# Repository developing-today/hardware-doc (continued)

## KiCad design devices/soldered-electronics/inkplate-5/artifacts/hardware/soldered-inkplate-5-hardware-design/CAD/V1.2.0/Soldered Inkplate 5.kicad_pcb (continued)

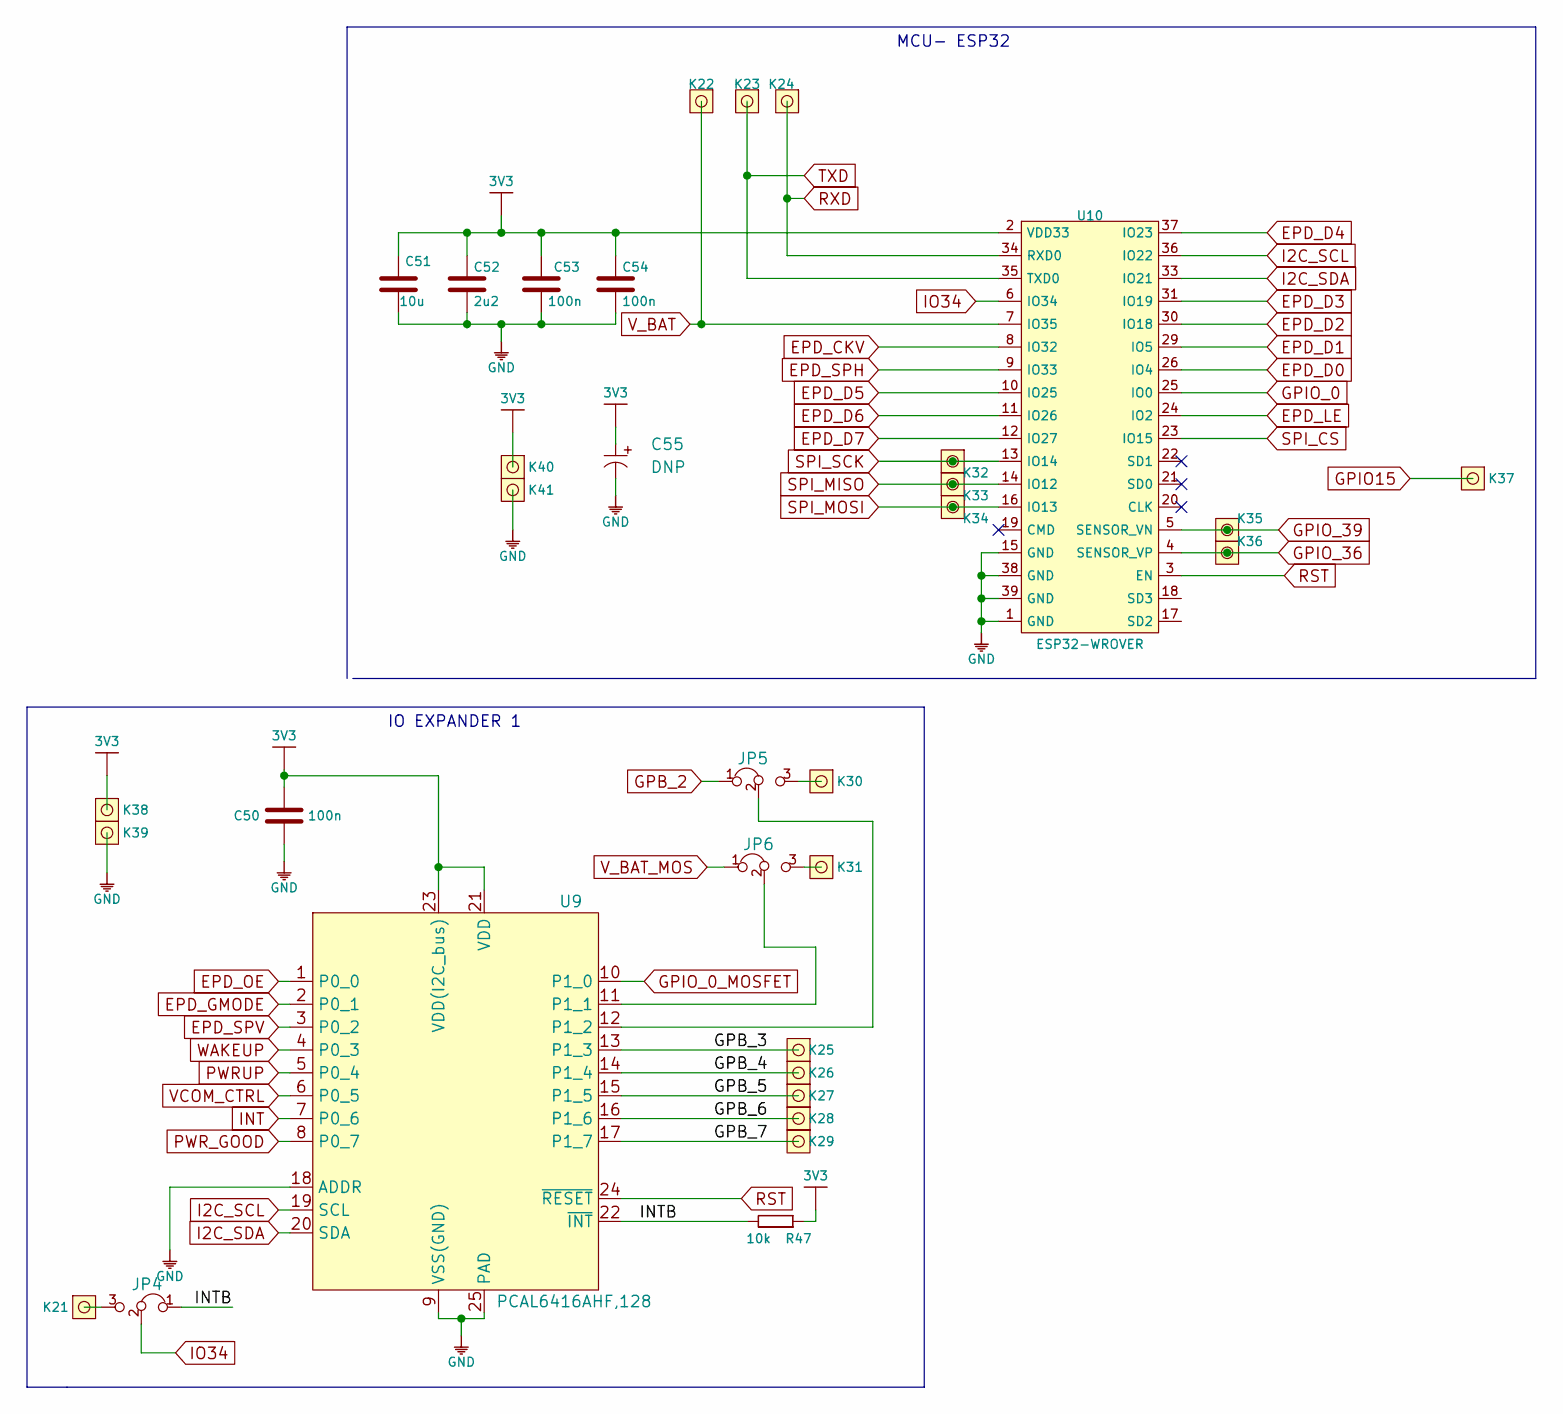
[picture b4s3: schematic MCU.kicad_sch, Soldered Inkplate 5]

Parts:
C50, C53, C54: 100n; 0603C
C51: 10u; 1206C
C52: 2u2; 0603C
C55: DNP; 2917C
JP4, JP5, JP6: SMD_JUMPER_3_PAD_CONNECTED_LEFT_TRACE
K21, K22, K23, K24, K25, K26, K27, K28, K29, K30, K31, K32, K33, K34, K35, K36, K37, K38, K39, K40, K41: HEADER_MALE_1X1_Inkplate
R47: 10k; 0603R
U9: PCAL6416AHF,128
U10: ESP32-WROVER

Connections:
3V3: C50.2, C51.2, C52.2, C53.2, C54.2, C55.1 (+), K38.1, K40.1, R47.1, U9.21 (VDD), U9.23 (VDD(I2C_bus)), U10.2 (VDD33); also elsewhere on the board
/MCU/GPB_3: K25.1, U9.13 (P1_3)
/MCU/GPB_4: K26.1, U9.14 (P1_4)
/MCU/GPB_5: K27.1, U9.15 (P1_5)
/MCU/GPB_6: K28.1, U9.16 (P1_6)
/MCU/GPB_7: K29.1, U9.17 (P1_7)
/MCU/INTB: JP4.1, R47.2, U9.22 (~INT)
EPD_CKV: U10.8 (IO32); also elsewhere on the board
EPD_D0: U10.26 (IO4); also elsewhere on the board
EPD_D1: U10.29 (IO5); also elsewhere on the board
EPD_D2: U10.30 (IO18); also elsewhere on the board
EPD_D3: U10.31 (IO19); also elsewhere on the board
EPD_D4: U10.37 (IO23); also elsewhere on the board
EPD_D5: U10.10 (IO25); also elsewhere on the board
EPD_D6: U10.11 (IO26); also elsewhere on the board
EPD_D7: U10.12 (IO27); also elsewhere on the board
EPD_GMODE: U9.2 (P0_1); also elsewhere on the board
EPD_LE: U10.24 (IO2); also elsewhere on the board
EPD_OE: U9.1 (P0_0); also elsewhere on the board
EPD_SPH: U10.9 (IO33); also elsewhere on the board
EPD_SPV: U9.3 (P0_2); also elsewhere on the board
GND: C50.1, C51.1, C52.1, C53.1, C54.1, C55.2 (-), K39.1, K41.1, U9.9 (VSS(GND)), U9.18 (ADDR), U9.25 (PAD), U10.1 (GND), U10.15 (GND), U10.38 (GND), U10.39 (GND); also elsewhere on the board
GPB_2: JP5.1; also elsewhere on the board
GPIO15: K37.1; also elsewhere on the board
GPIO_0: U10.25 (IO0); also elsewhere on the board
GPIO_0_MOSFET: U9.10 (P1_0); also elsewhere on the board
GPIO_36: K36.1, U10.4 (SENSOR_VP); also elsewhere on the board
GPIO_39: K35.1, U10.5 (SENSOR_VN); also elsewhere on the board
I2C_SCL: U9.19 (SCL), U10.36 (IO22); also elsewhere on the board
I2C_SDA: U9.20 (SDA), U10.33 (IO21); also elsewhere on the board
INT: U9.7 (P0_6); also elsewhere on the board
IO34: JP4.2, U10.6 (IO34)
unnamed: JP4.3, K21.1
unnamed: JP5.2, U9.12 (P1_2)
unnamed: JP5.3, K30.1
unnamed: JP6.2, U9.11 (P1_1)
unnamed: JP6.3, K31.1
PWRUP: U9.5 (P0_4); also elsewhere on the board
PWR_GOOD: U9.8 (P0_7); also elsewhere on the board
RST: U9.24 (~RESET), U10.3 (EN); also elsewhere on the board
RXD: K24.1, U10.34 (RXD0); also elsewhere on the board
SPI_CS: U10.23 (IO15); also elsewhere on the board
SPI_MISO: K33.1, U10.14 (IO12); also elsewhere on the board
SPI_MOSI: K34.1, U10.16 (IO13); also elsewhere on the board
SPI_SCK: K32.1, U10.13 (IO14); also elsewhere on the board
TXD: K23.1, U10.35 (TXD0); also elsewhere on the board
VCOM_CTRL: U9.6 (P0_5); also elsewhere on the board
V_BAT: K22.1, U10.7 (IO35); also elsewhere on the board
V_BAT_MOS: JP6.1; also elsewhere on the board
WAKEUP: U9.4 (P0_3); also elsewhere on the board

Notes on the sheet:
IO EXPANDER 1
MCU- ESP32

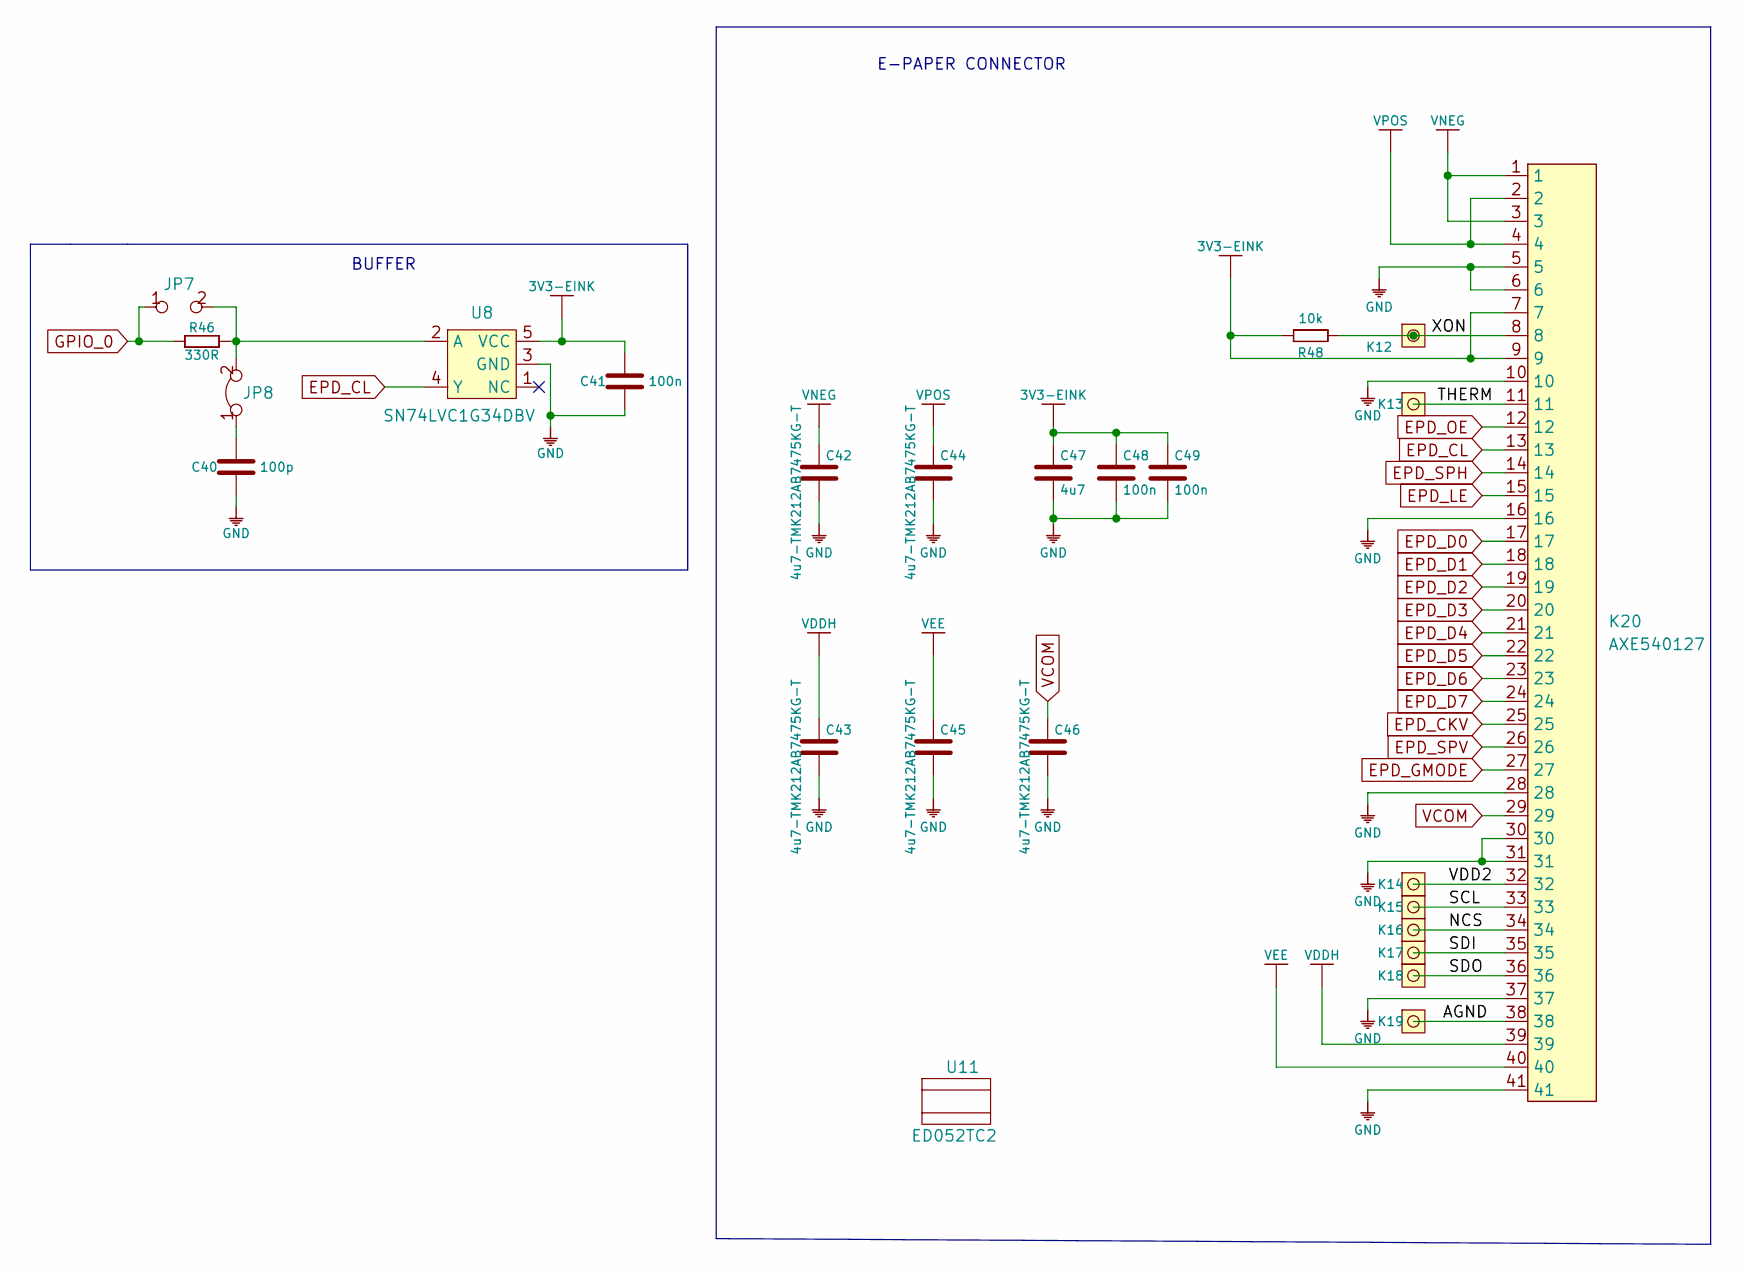
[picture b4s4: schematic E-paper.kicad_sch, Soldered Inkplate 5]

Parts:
C40: 100p; 0603C
C41, C48, C49: 100n; 0603C
C42, C43, C44, C45, C46: 4u7-TMK212AB7475KG-T; 0805C
C47: 4u7; 0603C
JP7: SMD_JUMPER
JP8: SMD-JUMPER-CONNECTED_TRACE_SOLDERMASK
K12, K13, K14, K15, K16, K17, K18, K19: HEADER_MALE_1X1_Inkplate
K20: AXE540127
R46: 330R; 0603R
R48: 10k; 0603R
U8: SN74LVC1G34DBV
U11: ED052TC2

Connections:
3V3-EINK: C41.2, C47.2, C48.2, C49.2, K20.7, K20.9, R48.1, U8.5 (VCC); also elsewhere on the board
/E-paper/AGND: K19.1, K20.38
/E-paper/NCS: K16.1, K20.34
/E-paper/SCL: K15.1, K20.33
/E-paper/SDI: K17.1, K20.35
/E-paper/SDO: K18.1, K20.36
/E-paper/THERM: K13.1, K20.11
/E-paper/VDD2: K14.1, K20.32
/E-paper/XON: K12.1, K20.8, R48.2
EPD_CKV: K20.25; also elsewhere on the board
EPD_CL: K20.13, U8.4 (Y)
EPD_D0: K20.17; also elsewhere on the board
EPD_D1: K20.18; also elsewhere on the board
EPD_D2: K20.19; also elsewhere on the board
EPD_D3: K20.20; also elsewhere on the board
EPD_D4: K20.21; also elsewhere on the board
EPD_D5: K20.22; also elsewhere on the board
EPD_D6: K20.23; also elsewhere on the board
EPD_D7: K20.24; also elsewhere on the board
EPD_GMODE: K20.27; also elsewhere on the board
EPD_LE: K20.15; also elsewhere on the board
EPD_OE: K20.12; also elsewhere on the board
EPD_SPH: K20.14; also elsewhere on the board
EPD_SPV: K20.26; also elsewhere on the board
GND: C40.1, C41.1, C42.1, C43.1, C44.1, C45.1, C46.1, C47.1, C48.1, C49.1, K20.5, K20.6, K20.10, K20.16, K20.28, K20.30, K20.31, K20.37, K20.41, U8.3 (GND); also elsewhere on the board
GPIO_0: JP7.1, R46.1; also elsewhere on the board
unnamed: C40.2, JP8.1
unnamed: JP7.2, JP8.2, R46.2, U8.2 (A)
VCOM: C46.2, K20.29; also elsewhere on the board
VDDH: C43.2, K20.39; also elsewhere on the board
VEE: C45.2, K20.40; also elsewhere on the board
VNEG: C42.2, K20.1, K20.3; also elsewhere on the board
VPOS: C44.2, K20.2, K20.4; also elsewhere on the board

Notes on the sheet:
E-PAPER CONNECTOR
BUFFER

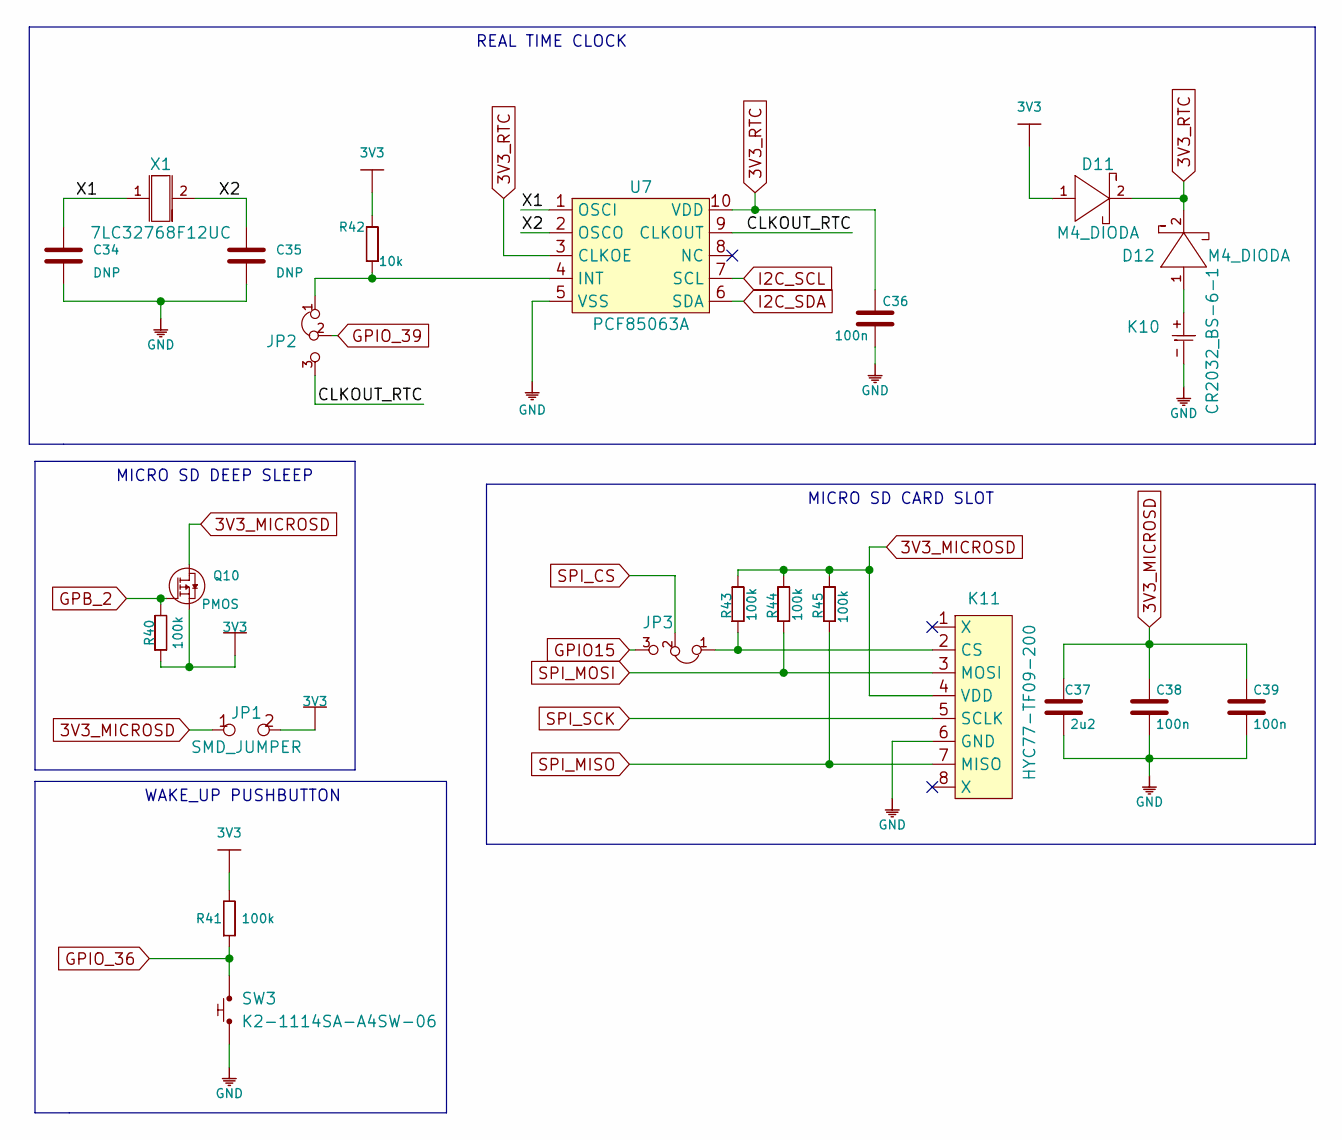
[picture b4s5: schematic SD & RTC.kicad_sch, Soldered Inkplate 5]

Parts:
C34, C35: DNP; 0603C
C36, C38, C39: 100n; 0603C
C37: 2u2; 0603C
D11, D12: M4_DIODA
JP1: SMD_JUMPER
JP2, JP3: SMD_JUMPER_3_PAD_CONNECTED_LEFT_TRACE
K10: CR2032_BS-6-1; CR2032-BS-6-1
K11: HYC77-TF09-200
Q10: PMOS; SOT-23-3
R40, R41, R43, R44, R45: 100k; 0603R
R42: 10k; 0603R
SW3: K2-1114SA-A4SW-06
U7: PCF85063A
X1: 7LC32768F12UC; ABS07AIG-32.768KHZ-7-D-T

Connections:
3V3: D11.1 (A), JP1.2, Q10.2 (S), R40.1, R41.2, R42.2; also elsewhere on the board
3V3_MICROSD: C37.2, C38.2, C39.2, JP1.1, K11.4 (VDD), Q10.3 (D), R43.2, R44.2, R45.2
3V3_RTC: C36.2, D11.2 (K), D12.2 (K), U7.3 (CLKOE), U7.10 (VDD)
/SD & RTC/CLKOUT_RTC: JP2.3, U7.9 (CLKOUT)
/SD & RTC/X1: C34.2, U7.1 (OSCI), X1.1
/SD & RTC/X2: C35.2, U7.2 (OSCO), X1.2
GND: C34.1, C35.1, C36.1, C37.1, C38.1, C39.1, K10.-, K11.6 (GND), SW3.1, U7.5 (VSS); also elsewhere on the board
GPB_2: Q10.1 (G), R40.2; also elsewhere on the board
GPIO15: JP3.3; also elsewhere on the board
GPIO_36: R41.1, SW3.2; also elsewhere on the board
GPIO_39: JP2.2; also elsewhere on the board
I2C_SCL: U7.7 (SCL); also elsewhere on the board
I2C_SDA: U7.6 (SDA); also elsewhere on the board
unnamed: D12.1 (A), K10.+
unnamed: JP2.1, R42.1, U7.4 (INT)
unnamed: JP3.1, K11.2 (CS), R43.1
SPI_CS: JP3.2; also elsewhere on the board
SPI_MISO: K11.7 (MISO), R45.1; also elsewhere on the board
SPI_MOSI: K11.3 (MOSI), R44.1; also elsewhere on the board
SPI_SCK: K11.5 (SCLK); also elsewhere on the board

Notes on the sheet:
REAL TIME CLOCK
MICRO SD CARD SLOT
WAKE_UP PUSHBUTTON
MICRO SD DEEP SLEEP

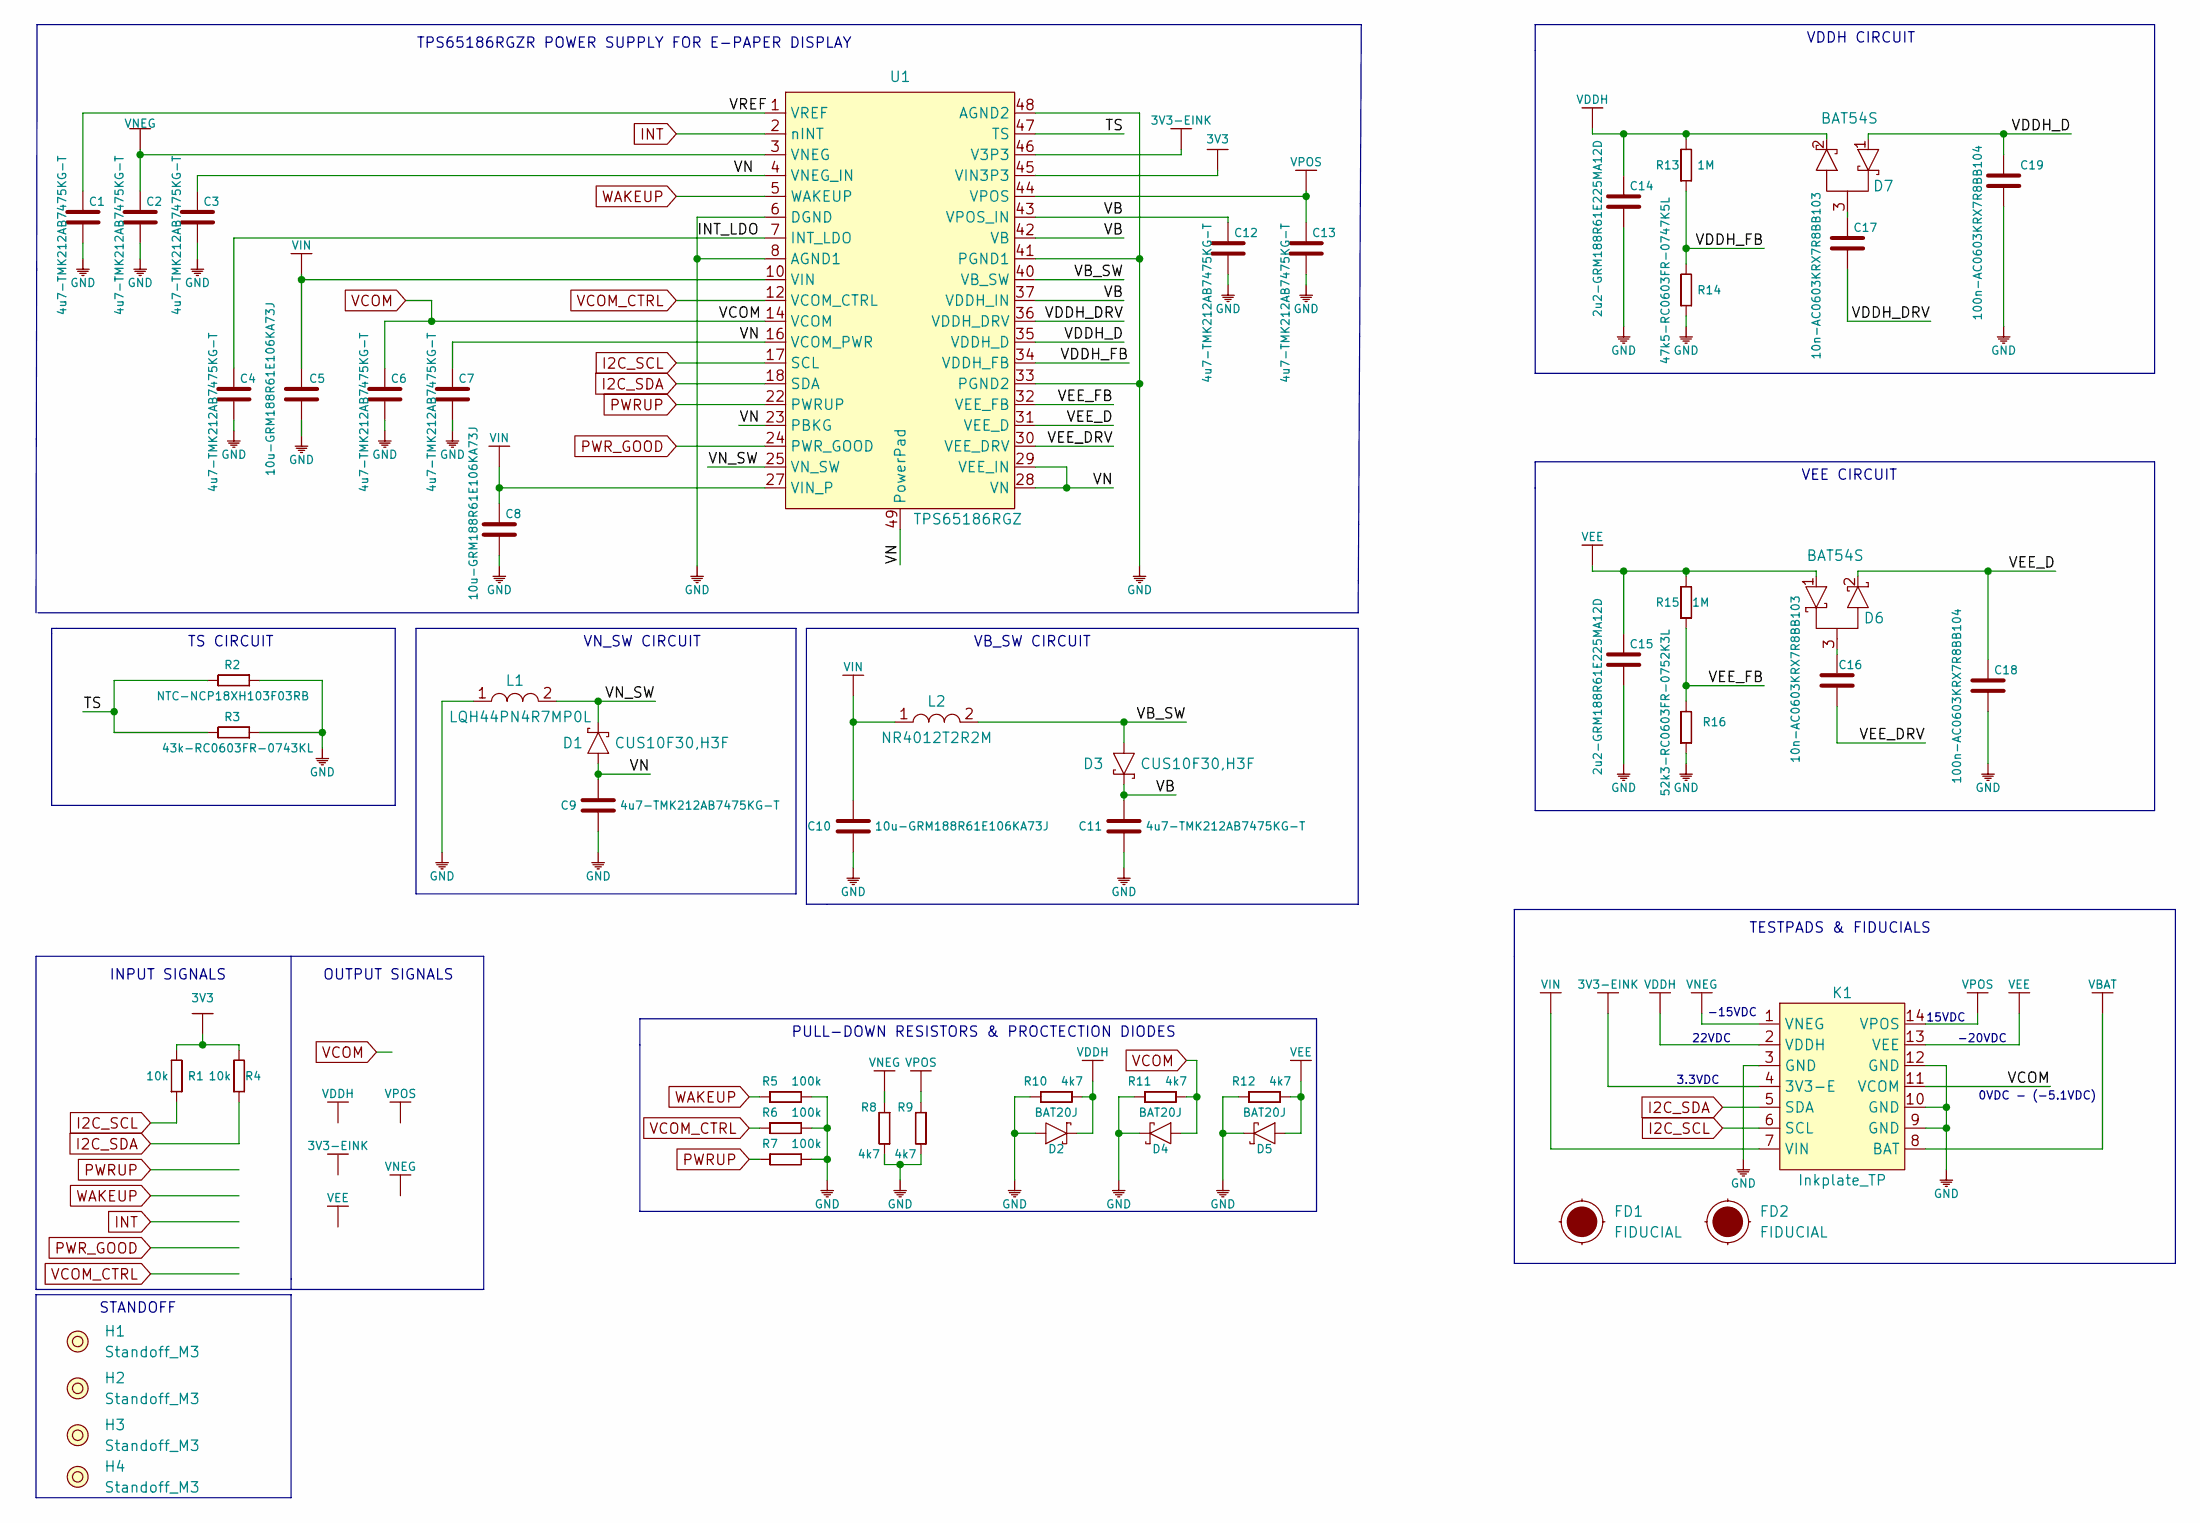
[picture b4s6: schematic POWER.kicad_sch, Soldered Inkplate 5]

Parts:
C1, C2, C3, C4, C6, C7, C9, C11, C12, C13: 4u7-TMK212AB7475KG-T; 0805C
C5, C8, C10: 10u-GRM188R61E106KA73J; 0603C
C14, C15: 2u2-GRM188R61E225MA12D; 0603C
C16, C17: 10n-AC0603KRX7R8BB103; 0603C
C18, C19: 100n-AC0603KRX7R8BB104; 0603C
D1, D3: CUS10F30,H3F; SOD-323-2
D2, D4, D5: BAT20J; SOD-323
D6, D7: BAT54S; SOT-23-3
FD1, FD2: FIDUCIAL; FIDUCIAL_23
H1, H2, H3, H4: Standoff_M3
K1: Inkplate_TP; INKPLATE TEST HEADER
L1: LQH44PN4R7MP0L; 1515L
L2: NR4012T2R2M; NR4012
R1, R4: 10k; 0603R
R2: NTC-NCP18XH103F03RB; 0603R
R3: 43k-RC0603FR-0743KL; 0603R
R5, R6, R7: 100k; 0603R
R8, R9, R10, R11, R12: 4k7; 0603R
R13, R15: 1M; 0603R
R14: 47k5-RC0603FR-0747K5L; 0603R
R16: 52k3-RC0603FR-0752K3L; 0603R
U1: TPS65186RGZ; VQFN-49

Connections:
3V3: R1.2, R4.2, U1.45 (VIN3P3); also elsewhere on the board
3V3-EINK: K1.4 (3V3-E), U1.46 (V3P3); also elsewhere on the board
/POWER/INT_LDO: C4.2, U1.7 (INT_LDO)
/POWER/TS: R2.2, R3.2, U1.47 (TS)
/POWER/VB: C11.1, C12.2, D3.1 (C), U1.37 (VDDH_IN), U1.42 (VB), U1.43 (VPOS_IN)
/POWER/VB_SW: D3.2 (A), L2.2, U1.40 (VB_SW)
/POWER/VDDH_D: C19.2, D7.1 (A), U1.35 (VDDH_D)
/POWER/VDDH_DRV: C17.1, U1.36 (VDDH_DRV)
/POWER/VDDH_FB: R13.1, R14.2, U1.34 (VDDH_FB)
/POWER/VEE_D: C18.2, D6.2 (K), U1.31 (VEE_D)
/POWER/VEE_DRV: C16.2, U1.30 (VEE_DRV)
/POWER/VEE_FB: R15.1, R16.2, U1.32 (VEE_FB)
/POWER/VN: C3.2, C7.2, C9.1, D1.2 (A), U1.4 (VNEG_IN), U1.16 (VCOM_PWR), U1.23 (PBKG), U1.28 (VN), U1.29 (VEE_IN), U1.49 (PowerPad)
/POWER/VN_SW: D1.1 (C), L1.2, U1.25 (VN_SW)
/POWER/VREF: C1.2, U1.1 (VREF)
GND: C1.1, C2.1, C3.1, C4.1, C5.1, C6.1, C7.1, C8.1, C9.2, C10.1, C11.2, C12.1, C13.1, C14.1, C15.1, C18.1, C19.1, D2.1 (A), D4.2 (C), D5.2 (C), K1.3 (GND), K1.9 (GND), K1.10 (GND), K1.12 (GND), L1.1, R2.1, R3.1, R5.2, R6.2, R7.2, R8.2, R9.2, R10.1, R11.1, R12.1, R14.1, R16.1, U1.6 (DGND), U1.8 (AGND1), U1.33 (PGND2), U1.41 (PGND1), U1.48 (AGND2); also elsewhere on the board
I2C_SCL: K1.6 (SCL), R1.1, U1.17 (SCL); also elsewhere on the board
I2C_SDA: K1.5 (SDA), R4.1, U1.18 (SDA); also elsewhere on the board
INT: U1.2 (nINT); also elsewhere on the board
unnamed: C16.1, D6.3
unnamed: C17.2, D7.3
PWRUP: R7.1, U1.22 (PWRUP); also elsewhere on the board
PWR_GOOD: U1.24 (PWR_GOOD); also elsewhere on the board
VBAT: K1.8 (BAT); also elsewhere on the board
VCOM: C6.2, D4.1 (A), K1.11 (VCOM), R11.2, U1.14 (VCOM); also elsewhere on the board
VCOM_CTRL: R6.1, U1.12 (VCOM_CTRL); also elsewhere on the board
VDDH: C14.2, D2.2 (C), D7.2 (K), K1.2 (VDDH), R10.2, R13.2; also elsewhere on the board
VEE: C15.2, D5.1 (A), D6.1 (A), K1.13 (VEE), R12.2, R15.2; also elsewhere on the board
VIN: C5.2, C8.2, C10.2, K1.7 (VIN), L2.1, U1.10 (VIN), U1.27 (VIN_P); also elsewhere on the board
VNEG: C2.2, K1.1 (VNEG), R8.1, U1.3 (VNEG); also elsewhere on the board
VPOS: C13.2, K1.14 (VPOS), R9.1, U1.44 (VPOS); also elsewhere on the board
WAKEUP: R5.1, U1.5 (WAKEUP); also elsewhere on the board

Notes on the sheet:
TS CIRCUIT
VDDH CIRCUIT
TESTPADS & FIDUCIALS
INPUT SIGNALS
-15VDC
VEE CIRCUIT
TPS65186RGZR POWER SUPPLY FOR E-PAPER DISPLAY
VN_SW CIRCUIT
0VDC - (-5.1VDC)
OUTPUT SIGNALS
15VDC
22VDC
PULL-DOWN RESISTORS & PROCTECTION DIODES
VB_SW CIRCUIT
STANDOFF
3.3VDC
-20VDC

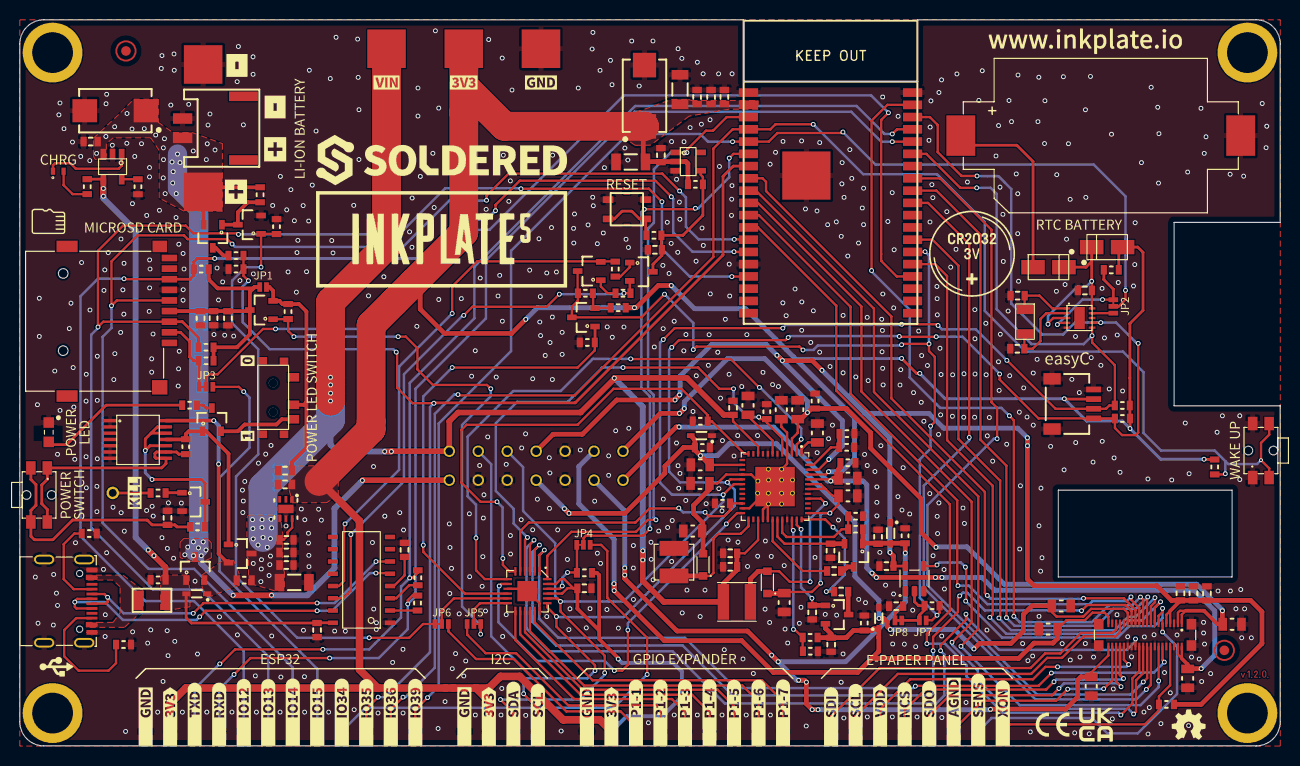
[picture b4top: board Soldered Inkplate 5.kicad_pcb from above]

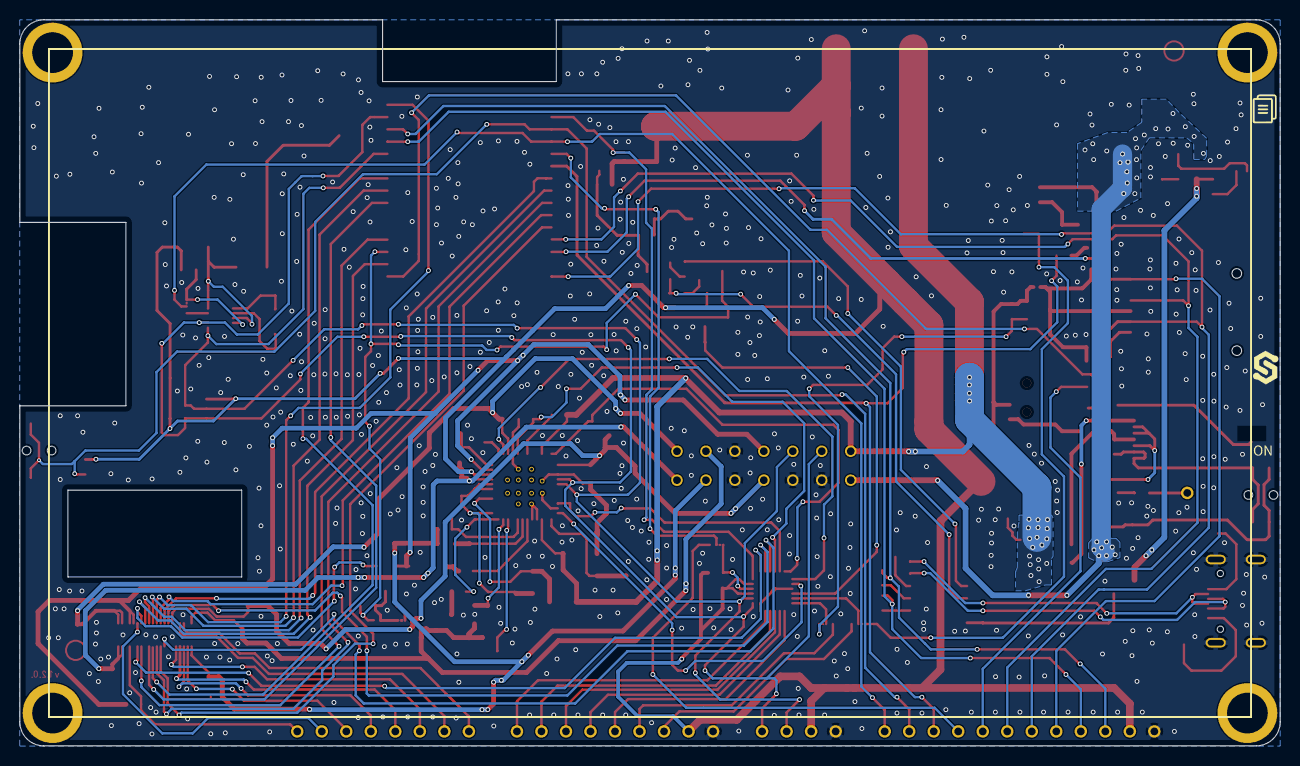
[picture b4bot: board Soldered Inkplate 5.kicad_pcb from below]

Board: 2 copper layers, 130.6 x 75.2 mm, 271 parts (2 on the bottom side), 123 nets.

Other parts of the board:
kibuzzard-63F8A516: G***; kibuzzard-63F8A516
kibuzzard-63F8A520: G***; kibuzzard-63F8A520
kibuzzard-63F89A5B: G***; kibuzzard-63F89A5B
kibuzzard-63F89A6D: G***; kibuzzard-63F89A6D
kibuzzard-63F89A8C: G***; kibuzzard-63F89A8C
kibuzzard-63F89A49: G***; kibuzzard-63F89A49
kibuzzard-63F89AA1: G***; kibuzzard-63F89AA1
kibuzzard-63F89AAD: G***; kibuzzard-63F89AAD
kibuzzard-63F89AB9: G***; kibuzzard-63F89AB9
kibuzzard-63F89AC1: G***; kibuzzard-63F89AC1
kibuzzard-63F89ACB: G***; kibuzzard-63F89ACB
kibuzzard-63F89AD4: G***; kibuzzard-63F89AD4
kibuzzard-63F89AE1: G***; kibuzzard-63F89AE1
kibuzzard-63F89AEB: G***; kibuzzard-63F89AEB
kibuzzard-63F89B1A: G***; kibuzzard-63F89B1A
kibuzzard-63F89B2E: G***; kibuzzard-63F89B2E
kibuzzard-63F89B38: G***; kibuzzard-63F89B38
kibuzzard-63F89B49: G***; kibuzzard-63F89B49
kibuzzard-63F89B54: G***; kibuzzard-63F89B54
kibuzzard-63F89B70: G***; kibuzzard-63F89B70
kibuzzard-63F89B77: G***; kibuzzard-63F89B77
kibuzzard-63F89B85: G***; kibuzzard-63F89B85
kibuzzard-63F89F9C: G***; kibuzzard-63F89F9C
kibuzzard-63F89F95: G***; kibuzzard-63F89F95
kibuzzard-63F89FA3: G***; kibuzzard-63F89FA3
kibuzzard-63F89FAA: G***; kibuzzard-63F89FAA
kibuzzard-63F896F5: G***; kibuzzard-63F896F5
kibuzzard-63F897A7: G***; kibuzzard-63F897A7
kibuzzard-63F897B8: G***; kibuzzard-63F897B8
kibuzzard-63F897D2: G***; kibuzzard-63F897D2
kibuzzard-63F897E2: G***; kibuzzard-63F897E2
kibuzzard-63F897FB: G***; kibuzzard-63F897FB
kibuzzard-63F898AB: G***; kibuzzard-63F898AB
kibuzzard-63F898C1: G***; kibuzzard-63F898C1
kibuzzard-63F898D0: G***; kibuzzard-63F898D0
kibuzzard-63F898D8: G***; kibuzzard-63F898D8
kibuzzard-63F898F1: G***; kibuzzard-63F898F1
kibuzzard-63F898FB: G***; kibuzzard-63F898FB
kibuzzard-63F899B9: G***; kibuzzard-63F899B9
kibuzzard-63F899CC: G***; kibuzzard-63F899CC
kibuzzard-63F899DF: G***; kibuzzard-63F899DF
kibuzzard-63F8971E: G***; kibuzzard-63F8971E
kibuzzard-63F8973B: G***; kibuzzard-63F8973B
kibuzzard-63F8983A: G***; kibuzzard-63F8983A
kibuzzard-63F8984A: G***; kibuzzard-63F8984A
kibuzzard-63F89702: G***; kibuzzard-63F89702
kibuzzard-63F89711: G***; kibuzzard-63F89711
kibuzzard-63F89728: G***; kibuzzard-63F89728
kibuzzard-63F89764: G***; kibuzzard-63F89764
kibuzzard-63F89780: G***; kibuzzard-63F89780
kibuzzard-63F89796: G***; kibuzzard-63F89796
kibuzzard-63F89823: G***; kibuzzard-63F89823
kibuzzard-63F89858: G***; kibuzzard-63F89858
kibuzzard-63F89870: G***; kibuzzard-63F89870
kibuzzard-63F89882: G***; kibuzzard-63F89882
kibuzzard-63F89892: G***; kibuzzard-63F89892
kibuzzard-63F89913: G***; kibuzzard-63F89913
kibuzzard-63F89923: G***; kibuzzard-63F89923
kibuzzard-63F89937: G***; kibuzzard-63F89937
kibuzzard-63F89944: G***; kibuzzard-63F89944
kibuzzard-63F89953: G***; kibuzzard-63F89953
kibuzzard-63F89964: G***; kibuzzard-63F89964
kibuzzard-63F89979: G***; kibuzzard-63F89979
kibuzzard-63F89994: G***; kibuzzard-63F89994
kibuzzard-63FCACFE: G***; kibuzzard-63FCACFE
kibuzzard-63FCAF1B: G***; kibuzzard-63FCAF1B
kibuzzard-63FCAF23: G***; kibuzzard-63FCAF23
